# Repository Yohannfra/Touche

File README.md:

# Touché

## Overview

Touché is a wireless scoring system for fencing based on **Arduino** and **nrf24l01**.

The goal is to make an **affordable**, **open source** and **open hardware** system.

⚠️  The capacitive touch feature (used to detect whether a hit landed on a conductive surface like the guard or a metallic piste, replacing the ground wires of a traditional setup) is currently very buggy and not usable, which makes the system hard to use with **foil**.

⚠️  Foil and  sabre support is in the roadmap but in a latter version that will certainly be on a different mcu (ESP32 or STM32).

#### The system is divided into 3 parts: one base station and two fencer boxes.

*During the early days of this project I called the base station the **server**
and the fencer boxes the **clients**, I will use this naming in this document
and across the project.*

## Getting started

To make a system you'll have to go through these steps:
1. Order the PCB and all the components
2. 3D print the boxes
3. Program the Arduino
4. Solder the PCB and assemble everything
5. Enjoy!

I wrote a step-by-step tutorial that you can find in [Assembly_Guide](./Assembly_Guide).

If you have a question about anything (please read the tutorial first) you can open a Github issue and I will try my best to answer you.

## About the directory structure

This repository contains all the **sources**, **3D files**, and **PCB files** needed to make this system.

```
.
├── Archive           # some old versions of the project
├── Documents         # pcb sources, and STL files
├── Code              # source code
├── Assembly_Guide/   # step by step tutorial to DIY
```
Each directory has its own README.md to explain this with more details.

## Roadmap

See Github issues.

## Contribute

If you have any improvement idea, find a bug or encounter a problem you can open a Github issue.

## License

All the code, CAD files, PCB files, and everything within this repository is licensed under the terms of the [GNU General Public License V3.0](./LICENSE).

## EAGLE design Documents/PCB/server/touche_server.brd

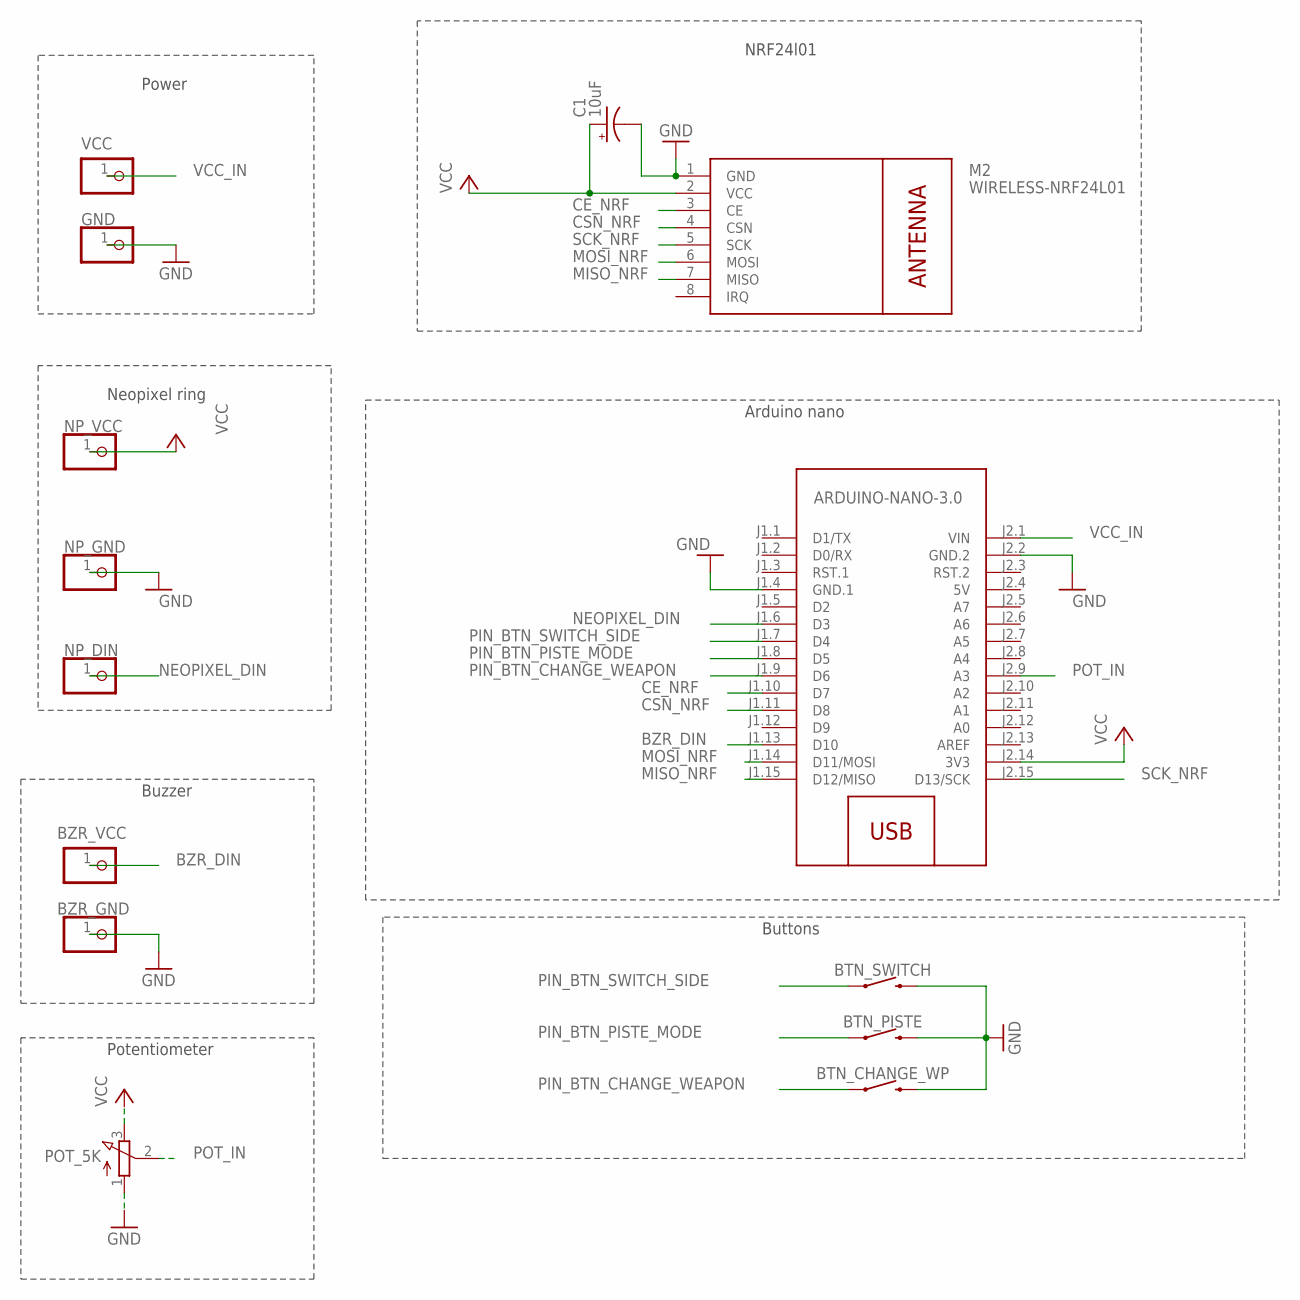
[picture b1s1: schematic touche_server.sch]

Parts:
BTN_CHANGE_WP: MOMENTARY-SWITCH-SPST-PTH-RIGHT-ANGLE-KIT; TACTILE_SWITCH_PTH_RIGHT_ANGLE_KIT
BTN_PISTE: MOMENTARY-SWITCH-SPST-PTH-RIGHT-ANGLE-KIT; TACTILE_SWITCH_PTH_RIGHT_ANGLE_KIT
BTN_SWITCH: MOMENTARY-SWITCH-SPST-PTH-RIGHT-ANGLE-KIT; TACTILE_SWITCH_PTH_RIGHT_ANGLE_KIT
BZR_GND: BZR_GND; 1X01
BZR_VCC: BZR_VCC; 1X01
C1: 10uF; E2-5
GND: GND; 1X01
M1: ARDUINO-NANO-3.0
M2: WIRELESS-NRF24L01
NP_DIN: NP_DIN; 1X01
NP_GND: NP_GND; 1X01
NP_VCC: NP_VCC; 1X01
POT_5K: 3RP/1610N
VCC: VCC; 1X01

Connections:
5V: M1.J2.4 (5V)
BZR_DIN: BZR_VCC.1, M1.J1.13 (D10)
CE_NRF: M1.J1.10 (D7), M2.3 (CE)
CSN_NRF: M1.J1.11 (D8), M2.4 (CSN)
GND: BTN_CHANGE_WP.2, BTN_PISTE.2, BTN_SWITCH.2, BZR_GND.1, C1.-, GND.1, M1.J1.4 (GND.1), M1.J2.2 (GND.2), M2.1 (GND), NP_GND.1, POT_5K.1 (A)
MISO_NRF: M1.J1.15 (D12/MISO), M2.7 (MISO)
MOSI_NRF: M1.J1.14 (D11/MOSI), M2.6 (MOSI)
NEOPIXEL_DIN: M1.J1.6 (D3), NP_DIN.1
PIN_BTN_CHANGE_WEAPON: BTN_CHANGE_WP.1, M1.J1.9 (D6)
PIN_BTN_PISTE_MODE: BTN_PISTE.1, M1.J1.8 (D5)
PIN_BTN_SWITCH_SIDE: BTN_SWITCH.1, M1.J1.7 (D4)
POT_IN: M1.J2.9 (A3), POT_5K.2 (S)
SCK_NRF: M1.J2.15 (D13/SCK), M2.5 (SCK)
VCC: C1.+, M1.J2.14 (3V3), M2.2 (VCC), NP_VCC.1, POT_5K.3 (E)
VCC_IN: M1.J2.1 (VIN), VCC.1

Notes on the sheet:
Potentiometer
Neopixel ring
Power
NRF24l01
Arduino nano
Buttons
Buzzer

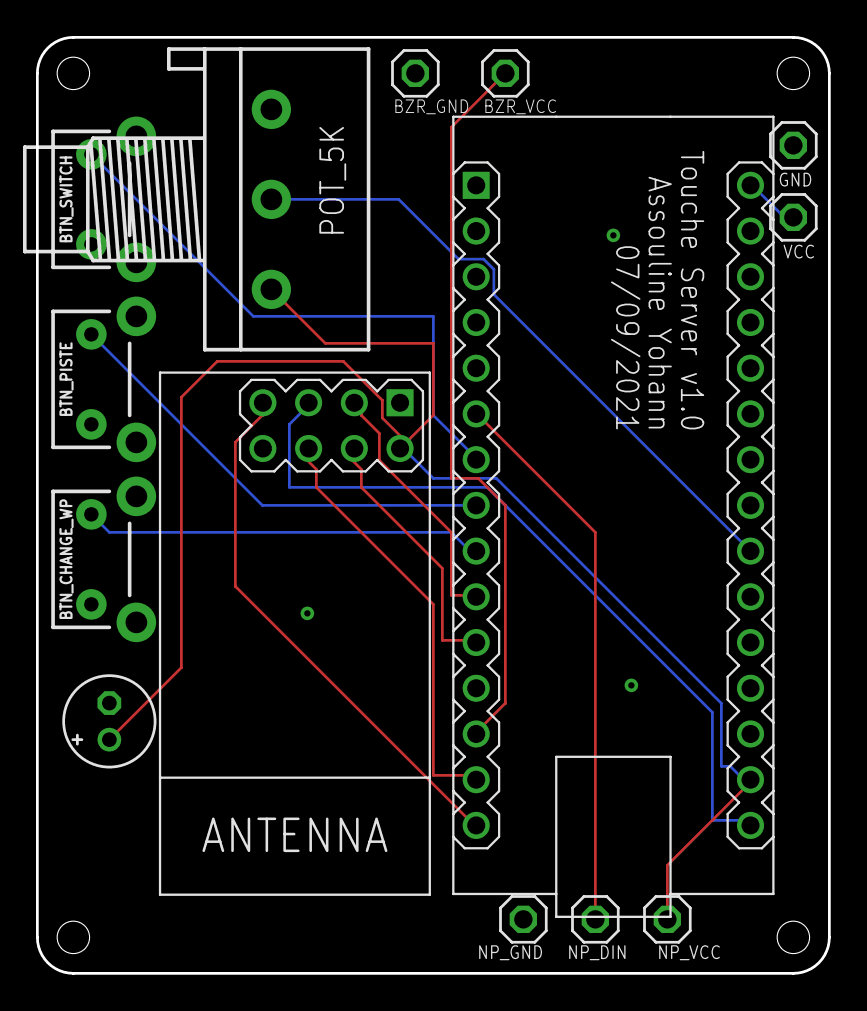
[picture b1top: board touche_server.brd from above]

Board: 2 copper layers, 44.0 x 52.0 mm, 14 parts (0 on the bottom side), 14 nets.

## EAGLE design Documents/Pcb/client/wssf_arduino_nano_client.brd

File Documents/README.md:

# Documents

This directory contains all CAD files, 3D files (STL), and PCB files.

````
.
├── CAD       # CAD and STL files for 3D printing
└── PCB       # PCB sources and gerber files
```

Each directory has its own README.md to explain this with more details.

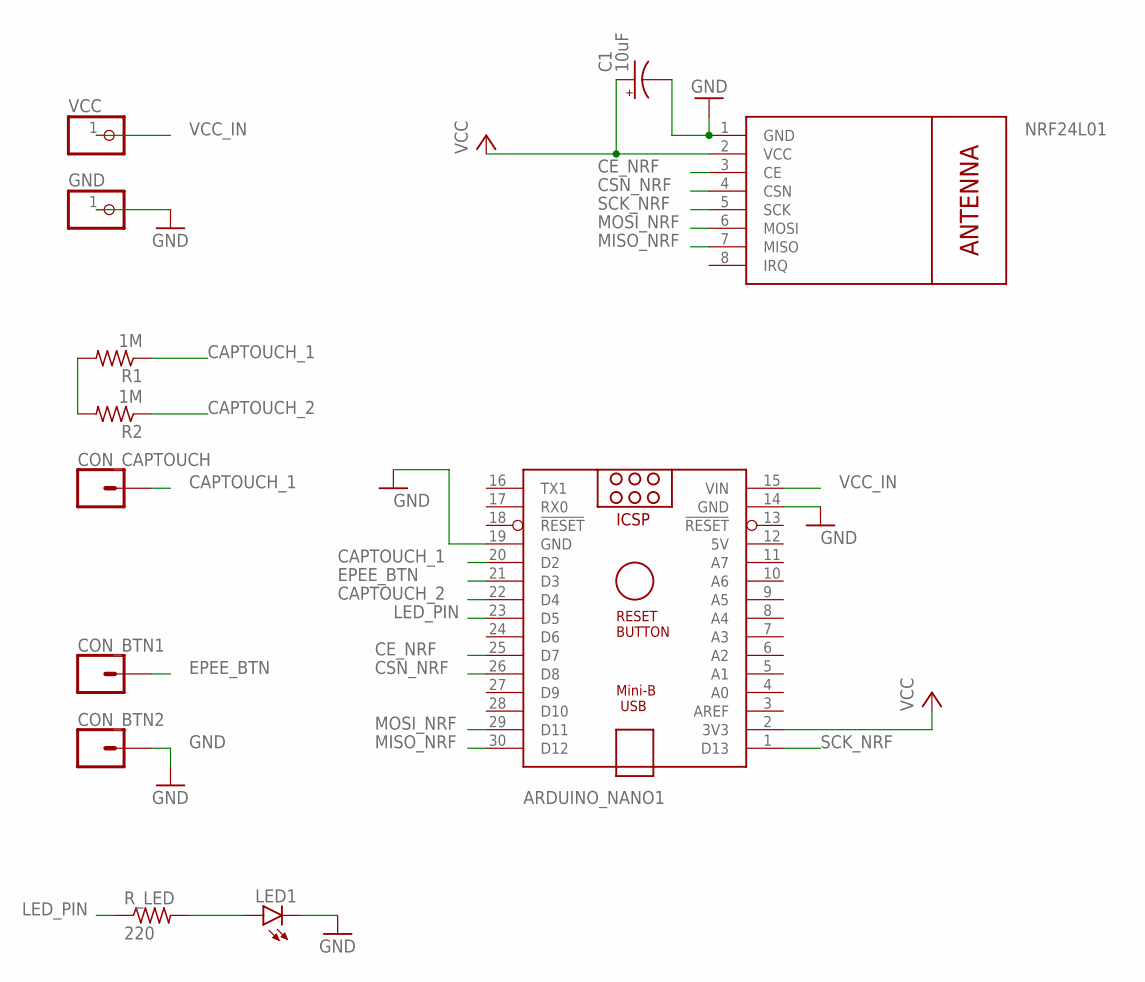
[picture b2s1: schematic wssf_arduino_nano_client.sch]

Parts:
ARDUINO_NANO1: ARDUINO_NANO
C1: 10uF; E2-5
CON_BTN1, CON_BTN2: CONN_01; 1X01
CON_CAPTOUCH: CONN_01; 1X01
GND: PINHD-1X1; 1X01
LED1: LED5MM
NRF24L01: WIRELESS-NRF24L01
R1, R2: 1M; 0204/7
R_LED: 220; 0204/7
VCC: PINHD-1X1; 1X01

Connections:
5V: ARDUINO_NANO1.12 (5V)
CAPTOUCH_1: ARDUINO_NANO1.20 (D2), CON_CAPTOUCH.1, R1.1
CAPTOUCH_2: ARDUINO_NANO1.22 (D4), R2.1
CE_NRF: ARDUINO_NANO1.25 (D7), NRF24L01.3 (CE)
CSN_NRF: ARDUINO_NANO1.26 (D8), NRF24L01.4 (CSN)
EPEE_BTN: ARDUINO_NANO1.21 (D3), CON_BTN1.1
GND: ARDUINO_NANO1.14 (GND), ARDUINO_NANO1.19 (GND), C1.-, CON_BTN2.1, GND.1, LED1.K (C), NRF24L01.1 (GND)
LED_PIN: ARDUINO_NANO1.23 (D5), R_LED.1
MISO_NRF: ARDUINO_NANO1.30 (D12), NRF24L01.7 (MISO)
MOSI_NRF: ARDUINO_NANO1.29 (D11), NRF24L01.6 (MOSI)
unnamed: LED1.A, R_LED.2
unnamed: R1.2, R2.2
SCK_NRF: ARDUINO_NANO1.1 (D13), NRF24L01.5 (SCK)
VCC: ARDUINO_NANO1.2 (3V3), C1.+, NRF24L01.2 (VCC)
VCC_IN: ARDUINO_NANO1.15 (VIN), VCC.1

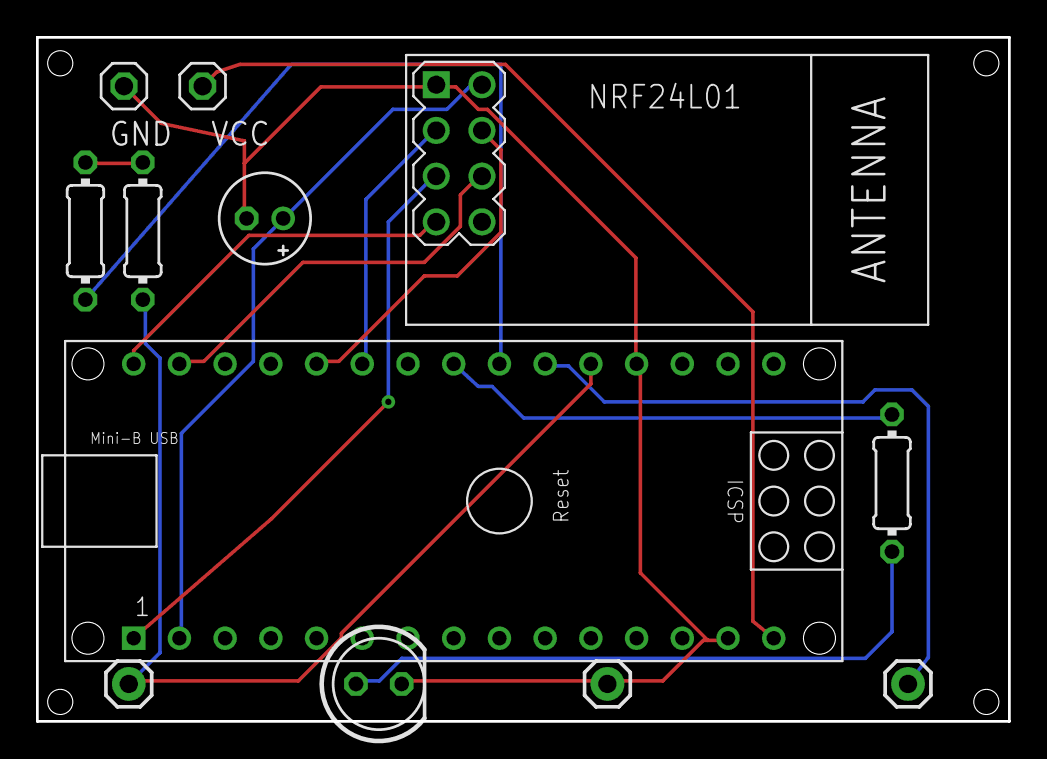
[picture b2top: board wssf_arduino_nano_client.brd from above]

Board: 2 copper layers, 54.0 x 38.0 mm, 12 parts (0 on the bottom side), 14 nets.

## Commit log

2019-09-12 Add README
2019-09-12 Add project files
2019-09-12 Add classes skeletons
2019-09-12 Update README and add a few code
2019-09-24 finished the basic code for the server and the client
2019-09-24 Create a class to handle the led matrix
2020-03-18 update client
2020-03-23 Add sandbox
2020-03-23 add doc and a sketch to print mac address
2020-03-23 add basic sketch using esp-now for client
2020-03-24 change all the build system, it now build using platformio
2020-03-24 change build system for the get_mac address too, move doc pictures to the doc folder and updates the platformio files
2020-03-24 rename directories
2020-03-24 add a shared directory for shared constants and defines
2020-03-24 update server and client sketches
2020-03-25 works with leds
2020-03-25 clean up shared constants files
2020-03-25 server now handle double hits
2020-03-25 add code for the buzzer
2020-03-29 fix typo in readme
2020-04-07 change digitalRead to analogRead to avoid the trigger when touching the pins
2020-04-07 change url for micro usb charger to an url for micro usb full circuit charge
2020-04-10 add code for led ring
2020-04-15 update server and clients
2020-04-24 start working on the ground
2020-04-24 remove headers from platformio files
2020-04-25 remove all headers
2020-04-25 add a diy tutorial
2020-04-25 add licence
2020-04-30 update diy tuto
2020-04-30 add video link to readme
2020-06-30 refactor the codebase to make it more readable
2020-06-30 Clean up the compilation and shared lib process
2020-06-30 Add constants file
2020-07-09 update for capsens
2020-07-11 update server
2020-07-11 update gitignore
2020-07-12 update server code for ground
2020-07-12 start idf client
2020-07-12 update esp idf client
2020-07-13 update esp idf client and fix watchdog bug
2020-07-19 update esp-idf client code
2020-07-20 fix esp now on esp idf client
2020-07-20 update arduino version for easier port
2020-07-20 add esp idf server
2020-07-21 update idf client
2020-07-25 clean client code
2020-08-01 update and fix esp idf server
2020-08-03 fix neopixels for server
2020-08-03 update baudrate client
2020-08-05 update client, messages are now send
2020-08-06 big update, now works with 2 clients, one red and the other green
2020-08-06 rename a few files and delete useless defines
2020-08-06 rename main files
2020-08-07 add basic captouch handling
2020-08-07 update server, ground touch now works
2020-08-07 finish esp idf migration
2020-08-07 add deep sleep for client
2020-08-10 add discrete color to neopixel handler
2020-08-10 split the code in multiples esp idf components
2020-08-10 split the code in multiples esp idf components (for the client this time)
2020-08-10 add get_state function to buzzer
2020-08-10 update server for ground to work even if hit msg arrived first
2020-08-10 fix bugs in server, it works :)
2020-08-10 move esp_now codes to components
2020-08-11 add esp_now logger tool
2020-08-11 move server mac address to a seperate file
2020-08-11 add code for external logger to server
2020-08-11 disable external logger by default
2020-08-27 update client with pcb pins
2020-09-04 fix compilation with new version of esp idf
2020-09-13 minor update after proto
2020-09-16 update client arduino nano code
2020-09-17 update arduino client
2020-09-17 add arduino server code
2020-09-21 fix ledring code for arduino client
2020-09-22 add function to light half of the neopixel
2020-11-29 update for pc
2020-11-29 add radiomodule code for client
2020-11-29 add radiomodule code for server
2020-11-30 fix client code
2020-11-30 add shared
2020-11-30 fix server code
2020-11-30 add blink on connection
2020-11-30 fix client id stuff
2020-11-30 add id and shared utils
2020-11-30 update ledring
2020-11-30 add double hit support
2020-11-30 add buzzer play
2020-12-01 add debug log lib
2020-12-01 add playermanager
2020-12-01 add protocol doc
2020-12-01 fix protocol doc
2020-12-01 add circle annimation
2020-12-01 cleanup server code
2020-12-01 reorganize server directory structure
2020-12-01 reorganize client directory structure
2020-12-02 rename button to epeebutton
2020-12-02 cleanup client code
2020-12-07 update led and button to use registers directly
2020-12-07 add function to print board infos
2020-12-07 fix board id printing
2020-12-07 update protocol
2020-12-08 save update
2020-12-09 add timer class
2020-12-09 fix potential bug in timer
2020-12-09 fix main and bugs with timers
2020-12-09 fix minor bug
2020-12-10 update all and fix bugs
2020-12-12 update button to use INPUT_PULLUP
2020-12-12 add sleepmanager
2020-12-13 update client build system to have debug and release
2020-12-13 update client makefile
2020-12-13 update client and add sleep after 5 mins
2020-12-13 update server build system to have debug and release
2020-12-13 update client coding style
2020-12-13 add a tool to open 3 screens at the same time
2020-12-13 remove ground stuff from server
2020-12-13 remove useless constants
2020-12-13 update fritzing schemas
2020-12-13 organise documentation folder
2020-12-14 update server fritzing
2020-12-14 rename folder old to archive and arduino nano code becomes main client and server
2020-12-14 update paths in platformio files
2020-12-15 add pcb files
2020-12-15 update gitignores
2020-12-22 update pcbs and add gerbers files
2020-12-28 update main README and add one for each folder
2020-12-28 document sources files of the client
2020-12-28 update doc in shared board_id
2021-01-28 fix range problem by sending the packet in a loop
2021-01-28 update server dependencies and delete unraleted doc
2021-01-28 fix board id problem using eeprom
2021-01-31 moved board id directory
2021-02-01 fix server compilation
2021-02-01 add github action
2021-02-01 remove tutorial files
2021-02-02 move old tools to archive
2021-02-02 add all builds to github action
2021-02-02 fix github action
2021-03-07 update client, rename captouch to virtualground
2021-03-07 update protocol file
2021-03-08 add a lot of doxygen documentation and comments
2021-03-09 add a lot of doxygen documentation and comments (in the server part)
2021-03-10 add second led ring support
2021-03-10 fix registration blink for two rings mode
2021-03-10 fix registration blink for two rings mode (again)
2021-03-15 Big update, change radio protocol and use 2 pipes, fix a few bugs here and there, remove id and use role instead
2021-03-15 fix compilation error
2021-03-15 update circle annimation function
2021-03-21 remove useless tools directory
2021-03-21 reorganise project file and directory structure
2021-03-22 add cad folder with client stl files
2021-03-22 update cad README
2021-03-22 rename Pcb to PCB and update README
2021-03-22 rename Pcb to PCB and update README 2
2021-03-22 rename Fritzing directory, add README and update client design
2021-03-22 update READMES
2021-03-22 add bom and empty instructable
2021-03-24 update virtualground code for epee and add a lot of inline documentation
2021-03-24 rename EpeeButton to WeaponButton
2021-03-24 fix write_role compilation
2021-03-30 change timer lib to shared and update client makefile
2021-04-02 update utils functions and add default weapon variable
2021-04-02 replace client basic led with rgb led
2021-04-04 add fclean and re rules to makefiles
2021-04-04 add server button class
2021-04-04 update ledRing class
2021-04-11 update protocol and server config
2021-04-13 big update for client and server
2021-04-13 fix client release compilation
2021-04-13 reorganise directory structure, delete useless fritzing schematics and update README
2021-04-15 add pcb sources and gerbers
2021-04-15 update Document's readme
2021-04-15 add basic piste detection
2021-04-18 add bidirectional communication between client and server
2021-04-18 Add license
2021-04-18 add license headers in source files
2021-04-21 add picture of the set to the readme
2021-04-21 rename instructable dir
2021-04-25 update PCBS and add screenshots
2021-04-25 update PCBS's readmes
2021-04-25 update CAD files and cad's README
2021-04-26 add clang format and fix bidirectional communication using ack instead
2021-04-26 rename weapon_mode to current_weapon
2021-04-27 rename all wsff to touche
2021-05-03 rename weapon_button to weapon, add arduino-log library and fix a few bugs
2021-05-03 start assembly guide
2021-05-03 add parts and tools needed in DIY guide
2021-05-03 fix dead link and rename diy guide file
2021-05-03 add pcb ordering to diy guide
2021-05-04 update guide
2021-05-04 update assembly guide
2021-05-09 replace DEBUG_LOG wit Log from ArduinoLog library
2021-05-12 add a debug log
2021-05-12 update on ack data
2021-05-13 update arduino-log version
2021-05-13 fix custom ack, it now works and fix a few bugs
2021-05-13 remove dead code
2021-05-19 apply weapon change for client
2021-05-19 apply weapon changes and buttons changes to server
2021-05-20 update serverConfig class to avoid global variables
2021-05-20 update mains
2021-05-20 update playerConfig to avoid globals variables
2021-05-20 create calibration.cpp for server
2021-05-22 update buzzer
2021-05-24 add serial.flush before serial.begin
2021-05-31 fix calibration animation
2021-05-31 fix client calibration process
2021-06-05 fix ack protocol
2021-06-05 fix bug in serverConfig and playerConfig
2021-06-05 add virtualGround reset function when changing weapon
2021-06-05 update led pins
2021-06-05 update server pins
2021-06-05 add function isPressed to weapon
2021-06-06 add assembly pictures
2021-06-06 update asembly readme
2021-06-06 update asembly guide
2021-06-07 update buzzer to use analog based on potentiometer value
2021-06-08 update double hit timing
2021-06-08 update actions management so it now sends invalid hit for foil
2021-06-10 update assembly readme
2021-06-10 update pcb
2021-06-10 update cad files
2021-06-11 add on/off indications on cad to show state
2021-06-12 update readme picture
2021-06-12 add debug define for buzzer
2021-06-12 set the number of samble for calibration to 50
2021-06-12 read register directly for button
2021-06-12 fix platformio dependency for RF24 lib
2021-06-12 fix bug with virtual ground reseted at every hit
2021-06-12 fix potentiometer values
2021-06-12 fix switch side action
2021-06-12 add archive readme
2021-06-12 update archive readme
2021-06-12 add Code directory's readme
2021-06-12 update Code directory's readme
2021-06-12 add shared directory readme
2021-06-12 add client directory readme
2021-06-12 add server directory readme
2021-06-12 fix typos
2021-06-18 fix foil button check
2021-06-18 remove useless delay in led blink
2021-06-18 remove useless delay in ledring::blink
2021-09-21 update PLAYER_ROLE definition to define it at build time
2021-09-23 fix typo in code closing #17
2022-02-20 Archive current version
2022-02-20 start nrf52840 version
2022-02-20 Add wip disclaimer in readme
2022-02-20 Simplify client main
2022-02-20 Add alive timer and led blinking
2022-02-23 Fix server app.overlay
2022-02-23 Fix led_ring driver functions
2022-02-23 Update server's main
2022-11-27 Add lint rule and fix cppcheck errors
2022-11-28 Typo in REAMDE
2022-11-28 Fix compilation error and change some const for constexpr
2022-11-28 Add compiledb rule to makefiles
2023-12-04 Compress main picture
2023-12-04 Add c++ version in cppcheck commands
2024-06-24 Add scripts
2024-08-11 Replace all 2021 with 2024 in licences
2026-06-10 Add claude.md file
2026-06-10 Add help rule to makefiles
2026-06-10 improve github build workflow
2026-06-10 Add a software retry after a nrf24.write if it fails and add some logs to see the fails
2026-06-10 improve claude doc, add section about the protocol

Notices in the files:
parts and their libraries:
SparkFun-Connectors: Licensing: Creative Commons ShareAlike 4.0 International - https://creativecommons.org/licenses/by-sa/4.0
diy-modules: Released under the Creative Commons Attribution 4.0 International License: http://creativecommons.org/licenses/by/4.0
